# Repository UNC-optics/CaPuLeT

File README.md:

# An open-source system to integrate Calcium-imaging, Pupillometry, and Locomotion-estimated Tracking (CaPuLeT) in head-fixed mice

Designed by members of the [Pégard](https://www.nicolaspegard.com/) and [Rodríguez-Romaguera](https://www.rodriguezromagueralab.org/) Labs at the University of North Carolina at Chapel Hill, **CaPuLeT** allows researchers to capture locomotion, pupil dynamics, and body kinematics simultaneously. Our system relies on CMOS cameras, an infrared camera placed at eye-level to capture pupil size and an additional camera to record body kinematics. Our system is capable of capturing  locomotion, or the mouse's movement across time, as our wheel system is attached to a mounted rotary encoder. For more information, refer to [Ortiz-Juza et al, 2024](https://star-protocols.cell.com/protocols/3752) [1].

# Graphic User Interface (GUI)

The **CaPuLeT** MATLAB graphical user interface (GUI) allows users to trigger and manage the cameras and LEDs driven by an Arduino microcontroller with a custom shield. Within **CaPuLeT**, users can track locomotion, pupil-size, and *in vivo* calcium imaging data in real-time. 

**Behavioral and Imaging Data Collected**:
- IR Camera → Pupil Dynamics (Dilation and Constriction)
- Additional Camera → Body Kinematics (Body and Tail Movement)
- Rotary Encoder → Locomotion (Speed and Acceleration)
- Multi-Photon Microscope → Neuronal Activity (Intracellular Calcium Concentration)

# Custom Arduino Printed Circuit Board Shield:
The head-fixation wheel system is driven and controlled by an Arduino Mega 2560 microcontroller board, with a custom printed circuit board (PCB) Arduino shield with built-in resistance, interactive feedback LEDs, real-time clock compatibility, and screw hole terminals. The printed circuit board shield expands the capabilities of the microcontroller board and allows for greater stability than a conventional solderless circuit board. The Arduino shield allows users to interface with each of the components of the **CaPuLeT** GUI. 

# Commercially Available and Custom Made Parts 

The following [component list](https://github.com/UNC-optics/CaPuLeT/blob/b9dc13ef048e2fede86db514f3f39af26186ab3a/1-CaPuLeT-Components-Table.pdf) details the manufacturer, part number, and quantity of each item required. This [version](https://github.com/UNC-optics/CaPuLeT/blob/b9dc13ef048e2fede86db514f3f39af26186ab3a/2-CaPuLeT-Color-Coded-Components-Table.pdf) of the component list contains a color coded key which provides an additional layer of support when building the system. 

<table class="table table-bordered table-hover table-condensed">
<thead><tr><th title="Field #1">Part Number</th>
<th title="Field #2">Distributor</th>
<th title="Field #3">Part Name</th>
<th title="Field #4">Distributor Part Number</th>
<th title="Field #5">Quantity Needed</th>
<th title="Field #6">Unit Price</th>
<th title="Field #7">Total Price</th>
</tr></thead>
<tbody><tr>
<td align="right">1</td>
<td>McMaster</td>
<td>5 mm Linear Motion Shaft</td>
<td>6112K37</td>
<td>1</td>
<td>$10.98 </td>
<td>$10.98 </td>
</tr>
<tr>
<td align="right">2</td>
<td>McMaster</td>
<td>Clear Impact-Resistant Polycarbonate Film</td>
<td>85585K15</td>
<td>1</td>
<td>$8.35 </td>
<td>$8.35 </td>
</tr>
<tr>
<td align="right">3</td>
<td>McMaster</td>
<td>Female Threaded Round Standoff</td>
<td>93330A541</td>
<td>10</td>
<td>$2.13 </td>
<td>$21.30 </td>
</tr>
<tr>
<td align="right">4</td>
<td>McMaster</td>
<td>Socket Head Screw M3 x 0.5 mm Thread, 6 mm Long</td>
<td>91290A111</td>
<td>1 (Pack of 100)</td>
<td>$10.91 </td>
<td>$10.91 </td>
</tr>
<tr>
<td align="right">5</td>
<td>Polulu</td>
<td>Aluminum Mounting Hub for 5mm Shaft</td>
<td>1203</td>
<td>1 (Pack of 2)</td>
<td>$18.90 </td>
<td>$18.90 </td>
</tr>
<tr>
<td align="right">6</td>
<td>Polulu</td>
<td>Machine Screw: #4-40, 1/2? Length, Phillips</td>
<td>1962</td>
<td>1 (Pack of 25)</td>
<td>$1.39 </td>
<td>$1.39 </td>
</tr>
<tr>
<td align="right">7</td>
<td>Thorlabs</td>
<td>0.75 Inch Post</td>
<td>TR075</td>
<td>1</td>
<td>$5.38 </td>
<td>$5.38 </td>
</tr>
<tr>
<td align="right">8</td>
<td>Thorlabs</td>
<td>2 Inch Post</td>
<td>TR2</td>
<td>2</td>
<td>$5.90 </td>
<td>$11.80 </td>
</tr>
<tr>
<td align="right">9</td>
<td>Thorlabs</td>
<td>3 Inch Post</td>
<td>TR3</td>
<td>2</td>
<td>$6.15 </td>
<td>$12.30 </td>
</tr>
<tr>
<td align="right">10</td>
<td>Thorlabs</td>
<td>4 Inch Post, 5 Pack</td>
<td>TR4-P5</td>
<td>1 (Pack of 5)</td>
<td>$30.00 </td>
<td>$30.00 </td>
</tr>
<tr>
<td align="right">11</td>
<td>Thorlabs</td>
<td>6 Inch Post</td>
<td>TR6</td>
<td>2</td>
<td>$8.09 </td>
<td>$16.18 </td>
</tr>
<tr>
<td align="right">12</td>
<td>Thorlabs</td>
<td>8 Inch Post</td>
<td>TR8</td>
<td>2</td>
<td>$9.69 </td>
<td>$19.38 </td>
</tr>
<tr>
<td align="right">13</td>
<td>Thorlabs</td>
<td>10 Inch Post</td>
<td>TR10</td>
<td>2</td>
<td>$10.76 </td>
<td>$21.52 </td>
</tr>
<tr>
<td align="right">14</td>
<td>Thorlabs</td>
<td>2 Inch Post Holder</td>
<td>PH2</td>
<td>1</td>
<td>$8.95 </td>
<td>$8.95 </td>
</tr>
<tr>
<td align="right">15</td>
<td>Thorlabs</td>
<td>3 Inch Post Holder</td>
<td>PH3</td>
<td>4</td>
<td>$9.62 </td>
<td>$38.48 </td>
</tr>
<tr>
<td align="right">16</td>
<td>Thorlabs</td>
<td>6 Inch Post Holder</td>
<td>PH6</td>
<td>1</td>
<td>$14.70 </td>
<td>$14.70 </td>
</tr>
<tr>
<td align="right">17</td>
<td>Thorlabs</td>
<td>Right Angle End Clamp</td>
<td>RA180</td>
<td>4</td>
<td>$12.34 </td>
<td>$49.36 </td>
</tr>
<tr>
<td align="right">18</td>
<td>Thorlabs</td>
<td>Rotating Clamp</td>
<td>SWC</td>
<td>1</td>
<td>$26.91 </td>
<td>$26.91 </td>
</tr>
<tr>
<td align="right">19</td>
<td>Thorlabs</td>
<td>Right Angle Post Clamp</td>
<td>RA90TR</td>
<td>1</td>
<td>$17.82 </td>
<td>$17.82 </td>
</tr>
<tr>
<td align="right">20</td>
<td>Thorlabs</td>
<td>Mini Optical Post</td>
<td>MS3R</td>
<td>1</td>
<td>$9.09 </td>
<td>$9.09 </td>
</tr>
<tr>
<td align="right">21</td>
<td>Thorlabs</td>
<td>Aluminum Breadboard 8&quot; x 10&quot; x 1/2&quot;, 1/4&quot;-20 Taps</td>
<td>MB810</td>
<td>1</td>
<td>$131.60 </td>
<td>$131.60 </td>
</tr>
<tr>
<td align="right">22</td>
<td>Thorlabs</td>
<td>Aluminum Breadboard 12&quot; x 18&quot; x 1/2&quot;, 1/4&quot;-20 Taps</td>
<td>MB1218</td>
<td>1</td>
<td>$214.65 </td>
<td>$214.65 </td>
</tr>
<tr>
<td align="right">23</td>
<td>Thorlabs</td>
<td>Breadboard Lifting Handles, Reinforced Polymer </td>
<td>BBH1</td>
<td>2 (Pack of 2)</td>
<td>$17.01 </td>
<td>$17.01 </td>
</tr>
<tr>
<td align="right">24</td>
<td>Thorlabs</td>
<td>4-40 Stainless Steel Cap Screw, 3/8&quot; Long</td>
<td>SH4S038</td>
<td>1 (Pack of 50)</td>
<td>$9.31 </td>
<td>$9.31 </td>
</tr>
<tr>
<td align="right">25</td>
<td>Thorlabs</td>
<td>Spring-Loaded 3/16&quot; Hex-Locking Thumbscrew, 1/4&quot;-20 Thread</td>
<td>TS25H</td>
<td>2</td>
<td>$2.87 </td>
<td>$5.74 </td>
</tr>
<tr>
<td align="right">26</td>
<td>Thorlabs</td>
<td>1/4&quot;-20 Stainless Steel Setscrew, 5/8&quot; Long (Adaptor)</td>
<td>SS25S0625</td>
<td>1 (Pack of 25)</td>
<td>$6.97 </td>
<td>$6.97 </td>
</tr>
<tr>
<td align="right">27</td>
<td>Thorlabs</td>
<td>1/4&quot; Washer, M6 Compatible, Stainless Steel</td>
<td>W25S050</td>
<td>1 (Pack of 100)</td>
<td>$10.20 </td>
<td>$10.20 </td>
</tr>
<tr>
<td align="right">28</td>
<td>Thorlabs</td>
<td>1/4&quot;-20 Stainless Steel Nut</td>
<td>N25S0440</td>
<td>1 (Pack of 50)</td>
<td>$6.43 </td>
<td>$6.43 </td>
</tr>
<tr>
<td align="right">29</td>
<td>Omron</td>
<td>Rotary Encoder - 1024 P/R (Quadrature)</td>
<td>E6B2-CWZ3E (E69-C06B)</td>
<td>1</td>
<td>$48.50 </td>
<td>$48.50 </td>
</tr>
<tr>
<td align="right">30</td>
<td>DB Unlimited</td>
<td>Speaker 80hm 5 w top port 104db</td>
<td>2104-SP500208-3-ND</td>
<td>1</td>
<td>$6.79 </td>
<td>$6.79 </td>
</tr>
<tr>
<td align="right">31</td>
<td>SullinsCorp</td>
<td>2.54mm Pitch Single Row Pin Header Strip</td>
<td>PREC040SAAN-RC</td>
<td>3</td>
<td>$1.53</td>
<td>$1.53</td>
</tr>
<tr>
<td align="right">32</td>
<td>Ardest</td>
<td>2N2222 NPN TO-92 Power Transistors</td>
<td>2N2222</td>
<td>6</td>
<td>$1.44</td>
<td>$1.44</td>
</tr>
<tr>
<td align="right">33</td>
<td>Boca Bearings</td>
<td>5 mm Steel Ball Bearing</td>
<td>SMR115-ZZC #5 LD</td>
<td>2</td>
<td>$10.58 </td>
<td>$21.16 </td>
</tr>
<tr>
<td align="right">34</td>
<td>Xenocam</td>
<td>9-22mm 1/3" F1.4 M12-mount lens with IR filter</td>
<td>XC0922LENS</td>
<td>1</td>
<td>$19.99 </td>
<td>$19.99 </td>
</tr>
<tr>
<td align="right">35</td>
<td>Monoprice</td>
<td>USB 2.0 Type-A Male to Mini-B 5pin Male Cable (Monoprice)</td>
<td>B002KL8J8W</td>
<td>1</td>
<td>$4.78</td>
<td>$4.78</td>
</tr>
<tr>
<td align="right">36</td>
<td>Computar</td>
<td>0.33-Inch Varifocal lens 2.8-12mm F1.3 Auto Iris (Computar)</td>
<td>B002HRE2ZS / TG4Z2813FCS-IR</td>
<td>1(Used)</td>
<td>$19.99 </td>
<td>$19.99 </td>
</tr>
<tr>
<td align="right">37</td>
<td>Chanzon</td>
<td>3 mm UV light, 395-400nm (Chanzon)</td>
<td>100F3T-YT-WH-PU</td>
<td>1 (Pack of 100)</td>
<td>$6.99 </td>
<td>$6.99 </td>
</tr>
<tr>
<td align="right">38</td>
<td>Adafruit</td>
<td>5 mm super-bright IR LED, 940nm (Adafruit)</td>
<td>ADA388 / B00ULB0U44</td>
<td>1 (Pack of 25)</td>
<td>$10.98 </td>
<td>$10.98 </td>
</tr>
<tr>
<td align="right">39</td>
<td>Fermerry</td>
<td>24 AWG 50 feet Electrical Wire (Fermerry)</td>
<td>B089CX3FVV</td>
<td>1</td>
<td>$26.99 </td>
<td>$26.99 </td>
</tr>
<tr>
<td align="right">40</td>
<td>Arduino</td>
<td>Arduino Mega 2560 Rev3 Microcontroller Board (Arduino)</td>
<td>A000067 / B0046AMGW0</td>
<td>1</td>
<td>$48.99 </td>
<td>$48.99 </td>
</tr>
<tr>
<td align="right">41</td>
<td>Arduino</td>
<td>USB 2.0 Cable Type A/B (Arduino)</td>
<td>M000006 / B013EOQUAW</td>
<td>1</td>
<td>$7.00 </td>
<td>$7.00 </td>
</tr>
<tr>
<td align="right">42</td>
<td>Tnisesm</td>
<td>PCB Mount Screw Terminal Block Connectors (Tnisesm)</td>
<td>CATN-T03B</td>
<td>1</td>
<td>$8.99 </td>
<td>$8.99 </td>
</tr>
<tr>
<td align="right">43</td>
<td>Adeep</td>
<td>Real Time Clock Module DS3231 AT24C32 IIC (Adeept)</td>
<td>2pcsDS3231 / B097PMNMQZ</td>
<td>1 (Pack of 2)</td>
<td>$7.99 </td>
<td>$7.99 </td>
</tr>
<tr>
<td align="right">44</td>
<td>LiCB</td>
<td>3V Lithium Battery (Junpower)</td>
<td>CR2032 / B07LGL9LQ1</td>
<td>1 (Pack of 10)</td>
<td>$4.99 </td>
<td>$4.99 </td>
</tr>
<tr>
<td align="right">45</td>
<td>ELECFUN</td>
<td>Heat Shrink Tubing (Electfun)</td>
<td>RSG-KIT350</td>
<td>1</td>
<td>$14.99 </td>
<td>$14.99 </td>
</tr>
<tr>
<td align="right">46</td>
<td>Yancorp</td>
<td>Black Adhesive contact paper (Yancorp)</td>
<td>B082CPSVPW</td>
<td>1</td>
<td>$6.98 </td>
<td>$6.98 </td>
</tr>
<tr>
<td align="right">47</td>
<td>Weld-On</td>
<td>IPS Weld-On 3 Acrylic Plastic Cement (Weld-On)</td>
<td>?TLLPN-21847771</td>
<td>1</td>
<td>$28.55 </td>
<td>$28.55 </td>
</tr>
<tr>
<td align="right">48</td>
<td>CENTROPOWER</td>
<td>12V 5A DC Power Cable Male Female Connector (Centro Power)</td>
<td>DCCORD-MF</td>
<td>1 (Pack of 10)</td>
<td>$9.19 </td>
<td>$9.19 </td>
</tr>
<tr>
<td align="right">49</td>
<td>CENTROPOWER</td>
<td>12V DC Power Connector Barrel Adaptor (Centro Power)</td>
<td>B07C61434H</td>
<td>1 (Pack of 10)</td>
<td>$7.99 </td>
<td>$7.99 </td>
</tr>
<tr>
<td align="right">50</td>
<td>ALITOVE</td>
<td>12V Red LED Flexible Strip Ribbon Light (Alitrove, 16.4 feet)</td>
<td>AL5RWPBK12V</td>
<td>1</td>
<td>$13.99 </td>
<td>$13.99 </td>
</tr>
<tr>
<td align="right">51</td>
<td>Mifasopower</td>
<td>Power Strip Surge Protector 10Ft (Mifaso Power)</td>
<td>MFS311T</td>
<td>1</td>
<td>$19.99 </td>
<td>$19.99 </td>
</tr>
<tr>
<td align="right">52</td>
<td>Sumato Stuff</td>
<td>Anti Vibration Pads (Functional Necessities)</td>
<td>SSHI00003</td>
<td>1 (Pack of 4)</td>
<td>$14.99 </td>
<td>$14.99 </td>
</tr>
<tr>
<td align="right">53</td>
<td>Focusound</td>
<td>1&quot; x 12&quot; x 12&quot; Sound Absorption Wall Panels (Xin &amp; Log)</td>
<td>FS0302A</td>
<td>1 (Pack of 24)</td>
<td>$17.99 </td>
<td>$17.99 </td>
</tr>
<tr>
<td align="right">54</td>
<td>TANTTI</td>
<td>4 inch Zip Ties with 18 lb Tensile Strength</td>
<td>604477847283</td>
<td>1 (Pack of 200)</td>
<td>$3.99 </td>
<td>$3.99 </td>
</tr>
<tr>
<td align="right">55</td>
<td>3M</td>
<td>3M Scotch Super 33+ Electrical Tape - 3/4 in x 52 ft</td>
<td>MMM06133</td>
<td>1</td>
<td>$4.98 </td>
<td>$4.98 </td>
</tr>
<tr>
<td align="right">56</td>
<td>Amazon</td>
<td>Hirose 4 Pin Female HR10A-7P-4S to Flying Leads Power Cable (Alvin’s Cables)</td>
<td>HR10A-7P-4S(73)</td>
<td>1</td>
<td>$25.99 </td>
<td>$25.99</td>
</tr>
<tr>
<td align="right">57</td>
<td>Custom Machined Parts</td>
<td>Rotary Encoder Adaptor (Aluminum 304)</td>
<td>CNC Machining (eMachineShop)</td>
<td>6 (Bulk Purchase)</td>
<td>$28.43 </td>
<td>$170.62 </td>
</tr>
<tr>
<td align="right">58</td>
<td>Custom Machined Parts</td>
<td>Head Plate Holder (Aluminum 304)</td>
<td>CNC Machining (eMachineShop)</td>
<td>12 (Bulk Purchase)</td>
<td>$30.20 </td>
<td>$362.44 </td>
</tr>
<tr>
<td align="right">59</td>
<td>Custom Machined Parts</td>
<td>Head Plate (Top Piece) (Aluminum 304)</td>
<td>CNC Machining (eMachineShop)</td>
<td>6 (Bulk Purchase)</td>
<td>$39.14 </td>
<td>$234.85 </td>
</tr>
<tr>
<td align="right">60</td>
<td>Custom Machined Parts</td>
<td>Head Plate (Bottom Piece) (Aluminum 304)</td>
<td>CNC Machining (eMachineShop)</td>
<td>6 (Bulk Purchase)</td>
<td>$51.01 </td>
<td>$306.04 </td>
</tr>
<tr>
<td align="right">61</td>
<td>Custom Machined Parts</td>
<td>Head rings (Aluminum 6061-T6)</td>
<td>CNC Machining (eMachineShop)</td>
<td>100 (Bulk Purchase)</td>
<td>$5.16 </td>
<td>$258.22 </td>
</tr>
<tr>
<td align="right">62</td>
<td>Custom Machined Parts</td>
<td>Rotary Wheel (1/8 Thick Clear Cast Acrylic)</td>
<td>Laser Cutting (Ponoko)</td>
<td>2</td>
<td>$61.06 </td>
<td>$61.06 </td>
</tr>
<tr>
<td align="right">63</td>
<td>Custom Machined Parts</td>
<td>Rotary Wheel Curved Surface (Clear Cast Acrylic)</td>
<td>Laser Cutting / Manual Cutting</td>
<td>1</td>
<td>$0.00 </td>
<td>$0.00 </td>
</tr>
<tr>
<td align="right">64</td>
<td>Custom Machined Parts</td>
<td>Rotary Wheel Curved Surface (Black Adhesive Contact Paper)</td>
<td>Laser Cutting / Manual Cutting</td>
<td>1</td>
<td>$0.00 </td>
<td>$0.00 </td>
</tr>
<tr>
<td align="right">65</td>
<td>Custom Machined Parts</td>
<td>Waste Management Ramp (Resin)</td>
<td>3-D Printing (Craftcloud3d)</td>
<td>1</td>
<td>$57.76 </td>
<td>$57.76 </td>
</tr>
<tr>
<td align="right">66</td>
<td>Custom Machined Parts</td>
<td>Arduino Mega 2560 Rev3 Protective Case (Resin)</td>
<td>3-D Printing (Craftcloud3d)</td>
<td>1</td>
<td>$16.06 </td>
<td>$16.06 </td>
</tr>
<tr>
<td align="right">67</td>
<td>Custom Machined Parts</td>
<td>Arduino Mega 2560 Rev3 Shield SMT PCB</td>
<td>PCB Manufacturing (JLC PCB)</td>
<td>1</td>
<td>X</td>
<td>X</td>
</tr>
<tr>
<td align="right">68</td>
<td>FLIR</td>
<td>Firefly S Camera</td>
<td>FFY-U3-16S2M-S</td>
<td>1</td>
<td>$234.00 </td>
<td>$234.00 </td>
</tr>
<tr>
<td align="right">69</td>
<td>FLIR</td>
<td>Tripod Adapter for Firefly S Camera</td>
<td>ACC-01-0017</td>
<td>1</td>
<td>$32.10 </td>
<td>$32.10 </td>
</tr>
<tr>
<td align="right">70</td>
<td>FLIR</td>
<td>USB 3.1 Locking Cable</td>
<td>ACC-01-2300</td>
<td>1</td>
<td>$24.60 </td>
<td>$24.60 </td>
</tr>
<tr>
<td align="right">71</td>
<td>FLIR</td>
<td>GPIO cable w/ 6 pins</td>
<td>ACC-01-3015</td>
<td>1</td>
<td>$9.60 </td>
<td>$9.60 </td>
</tr>
<tr>
<td align="right">72</td>
<td>The Imaging Source</td>
<td>USB 2.0 CMOS Monochrome Camera</td>
<td>DMK-22BUC03</td>
<td>1</td>
<td>$234.00 </td>
<td>$234.00 </td>
</tr>
<tr>
<td align="right">73</td>
<td>SYSRACKS</td>
<td>15U 35&quot; Depth Under Desk Sound Proof Server Cabinet</td>
<td>SP15.900</td>
<td>1</td>
<td>$1,122.00 </td>
<td>$1,122.00 </td>
</tr>
</tbody></table>

This [document](https://github.com/UNC-optics/CaPuLeT/blob/b9dc13ef048e2fede86db514f3f39af26186ab3a/4-CaPuLeT-Custom-Parts-Table.pdf) outlines the design of each of the custom pieces and the file types found within this repository that can be used to replicate the system. More details regarding the specifications of the custom parts can be found [here](https://github.com/UNC-optics/CaPuLeT/blob/b9dc13ef048e2fede86db514f3f39af26186ab3a/5-CaPuLeT-Custom-Parts-Specifications.pdf). The following [spreadsheet](https://github.com/UNC-optics/CaPuLeT/blob/b9dc13ef048e2fede86db514f3f39af26186ab3a/3-CaPuLeT-Cost-Spreadsheet.xlsx) outlines the total cost of the system.  

**Here is a list of the manufacturers we purchased materials from:** 
- McMaster-Carr
- Pololu
- Thorlabs
- SparkFun
- Digikey
- Amazon
- FLIR
- The Imaging Source
- SYSRACKS

**Here is a list of companies you can purchase custom parts from, if not fabricated in-house:**
- eMachineShop (CNC Machining)
- Ponoko (Laser Cutting)
- Craftcloud3d (3-D Printing)
- JBL PCB (PCB Printing / Soldering)

# Step-by-Step Building Guide

**A fully functioning system requires users to build the following elements from the materials purchased:**
- Locomotion Wheel
- Headplate Fixation System
- IR / UV LEDs

**Additionally, the following commercial materials need to modified to be used within our system:**
- Rotary Encoder
- GPIO Cable
- Hirose Cable
- Overhead Speaker
- Ambient Noise Fan
- Red LED Strips

This following [guide](https://github.com/UNC-optics/CaPuLeT/blob/b9dc13ef048e2fede86db514f3f39af26186ab3a/6-CaPuLeT-Step-by-Step-Guide.pdf) provides a step-by-step walkthrough for building and modifying each of the required components. This document includes diagrams and explanations for assembling each of the final components of the build. 

# Software Installation Guide and Dependencies

Following this installation guide will ensure that your system will be able to run the set of MATLAB scripts and Arduino IDE sketches we have provided. Our system is run primarily on MATLAB's interface. While other software is used to first initialize components, such as Arduino IDE for the rotary encoder and Spinnaker SDK for the cameras, the subsequent input signals and data acquisition steps are performed exclusively with MATLAB. 

**Required Software and Applications**:
- [MATLAB R2022a](https://www.mathworks.com/products/new_products/release2022a.html)
- [Arduino IDE](https://www.arduino.cc/en/software)
- [Spinnaker SDK](https://www.flir.com/products/spinnaker-sdk/)
- [DeepLabCuts](https://github.com/DeepLabCut/DeepLabCut)
  
Our MATLAB scripts are based on MATLAB R2022a, a previous version of the software application. Running our scripts on a more recent version of the application will result in a number of errors. After downloading MATLAB R2022a, you will need to download a number of toolboxes and add-ons. 

**Base Toolboxes**:
- Data Acquisition Toolbox
- Image Acquisition Toolbox
- Image Processing Toolbox
- Statistics and Machine Learning Toolbox 

**Additional Toolbox Support Packages**:
- Data Acquisition Toolbox Support Package for National Instruments NI-DAQmx Devices
- Image Acquisition Toolbox Support Package for GenICam Interface
- Image Acquisition Toolbox Support Package OS Generic Video Interface
- Image Acquisition Toolbox Support Package for Point Grey Hardware
- Image Acquisition Toolbox Support Support Package for GigE Vision Hardware
- MATLAB Support Package for Arduino Hardware

Finally, users will need to download the following drivers to generate a connection between their computer system and an external hardware device. In our case, we need to download two drivers to interface with the additional camera used in our system.

**Driver Requirements**:
- USB3 Driver
- [DMK 22BUC03 Driver](https://www.oemcameras.com/dmk-22buc03.htm)
- [Spinnaker SDK USB3 Vision Cameras Driver](https://www.flir.com/products/spinnaker-sdk/)
- [IC Matlab Plugin for Matlab (Version 3.4.0.58)](https://www.theimagingsource.com/en-us/support/download/icmatlabr2013b-3.4.0.58/)

**Library Requirements**:
- [DS3231 Library](https://github.com/NorthernWidget/DS3231)
  
# Contact

Further information and requests for resources should be directed to and will be fulfilled by the lead contact and corresponding author, Jose Rodriguez-Romaguera (jose_rodriguezromaguera@med.unc.edu). Example pupillometric and locomotion data is available upon request to the technical contact and corresponding author, Nicolas C. Pégard (pegard@unc.edu).

# Citation 

If you replicate this system in your own labs or use parts of our designs and code, we kindly ask that you please cite [Ortiz-Juza et al, 2024](https://star-protocols.cell.com/protocols/3752) [1]. 

[1] Ortiz-Juza, M. M., Tormes-Vaquerano, J., Hegel, S. M., Curtis, V. R., Alghorazi, R. A., Miller, N. W., McTaggart, E. M., Pégard, N. C., & Rodriguez-Romaguera, J. (2024). Protocol for an open-source system to integrate calcium imaging, pupillometry, and locomotion-estimated tracking in head-fixed mice. STAR Protocols, 5(4), 103331. https://doi.org/10.1016/j.xpro.2024.103331

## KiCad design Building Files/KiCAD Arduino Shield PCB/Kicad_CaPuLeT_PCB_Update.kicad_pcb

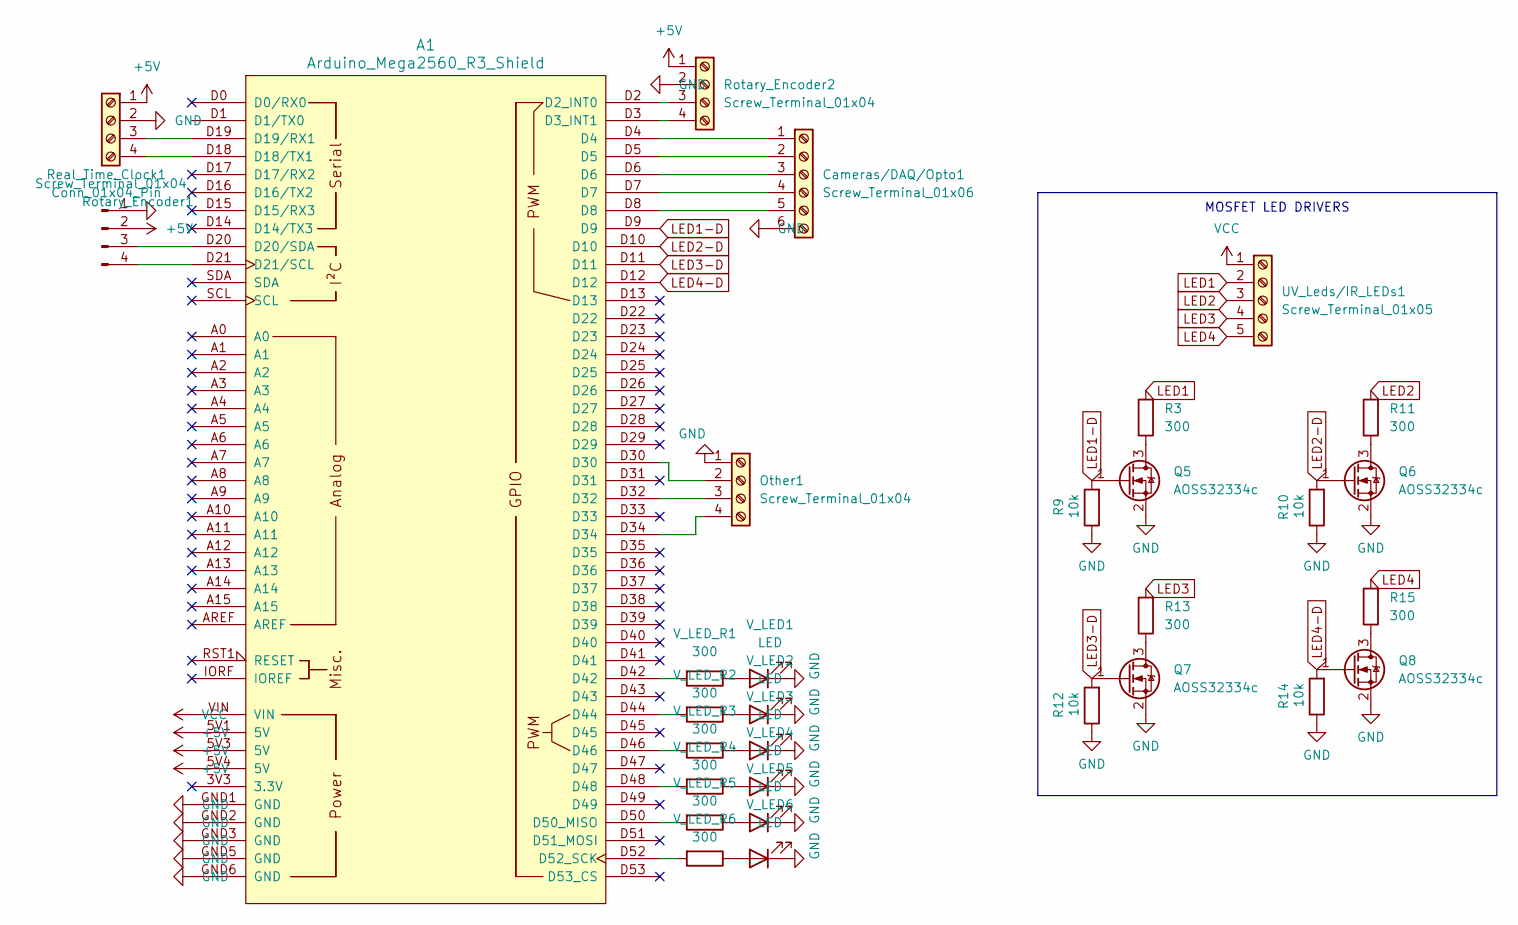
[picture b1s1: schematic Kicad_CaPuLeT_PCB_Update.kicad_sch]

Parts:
A1: Arduino_Mega2560_R3_Shield; Arduino_Mega2560_R3_Shield_Reduced_Hole
Cameras/DAQ/Opto1: Screw_Terminal_01x06; TerminalBlock_Phoenix_MKDS-1,5-6_1x06_P5.00mm_Horizontal
Other1: Screw_Terminal_01x04; TerminalBlock_Phoenix_MKDS-1,5-4_1x04_P5.00mm_Horizontal
Q5, Q6, Q7, Q8: AOSS32334c; SOT-23
R3, R11, R13, R15: 300; R_0805_2012Metric
R9, R10, R12, R14: 10k; R_0805_2012Metric
Real_Time_Clock1: Conn_01x04_Pin; PinHeader_1x04_P2.54mm_Vertical
Rotary_Encoder1, Rotary_Encoder2: Screw_Terminal_01x04; TerminalBlock_Phoenix_MKDS-1,5-4_1x04_P5.00mm_Horizontal
UV_Leds/IR_LEDs1: Screw_Terminal_01x05; TerminalBlock_Phoenix_MKDS-1,5-5_1x05_P5.00mm_Horizontal
V_LED1, V_LED2, V_LED3, V_LED4, V_LED5, V_LED6: LED; LED_0805_2012Metric
V_LED_R1, V_LED_R2, V_LED_R3, V_LED_R4, V_LED_R5, V_LED_R6: 300; R_0805_2012Metric

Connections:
+5V: A1.5V1 (5V), A1.5V3 (5V), A1.5V4 (5V), Real_Time_Clock1.2, Rotary_Encoder1.1, Rotary_Encoder2.1
GND: A1.GND1 (GND), A1.GND2 (GND), A1.GND3 (GND), A1.GND5 (GND), A1.GND6 (GND), Cameras/DAQ/Opto1.6, Other1.1, Q5.2 (S), Q6.2 (S), Q7.2 (S), Q8.2 (S), R9.1, R10.1, R12.1, R14.1, Real_Time_Clock1.1, Rotary_Encoder1.2, Rotary_Encoder2.2, V_LED1.1 (K), V_LED2.1 (K), V_LED3.1 (K), V_LED4.1 (K), V_LED5.1 (K), V_LED6.1 (K)
LED1: R3.2, UV_Leds/IR_LEDs1.2
LED1-D: A1.D9, Q5.1 (G), R9.2
LED2: R11.2, UV_Leds/IR_LEDs1.3
LED2-D: A1.D10, Q6.1 (G), R10.2
LED3: R13.2, UV_Leds/IR_LEDs1.4
LED3-D: A1.D11, Q7.1 (G), R12.2
LED4: R15.2, UV_Leds/IR_LEDs1.5
LED4-D: A1.D12, Q8.1 (G), R14.2
unnamed: A1.D2 (D2_INT0), Rotary_Encoder2.3
unnamed: A1.D3 (D3_INT1), Rotary_Encoder2.4
unnamed: A1.D18 (D18/TX1), Rotary_Encoder1.4
unnamed: A1.D19 (D19/RX1), Rotary_Encoder1.3
unnamed: A1.D20 (D20/SDA), Real_Time_Clock1.3
unnamed: A1.D21 (D21/SCL), Real_Time_Clock1.4
unnamed: A1.D50 (D50_MISO), V_LED_R5.2
unnamed: A1.D52 (D52_SCK), V_LED_R6.2
unnamed: A1.D42, V_LED_R1.2
unnamed: A1.D44, V_LED_R2.2
unnamed: A1.D46, V_LED_R3.2
unnamed: A1.D48, V_LED_R4.2
unnamed: A1.D4, Cameras/DAQ/Opto1.1
unnamed: A1.D5, Cameras/DAQ/Opto1.2
unnamed: A1.D6, Cameras/DAQ/Opto1.3
unnamed: A1.D7, Cameras/DAQ/Opto1.4
unnamed: A1.D8, Cameras/DAQ/Opto1.5
unnamed: A1.D30, Other1.2
unnamed: A1.D32, Other1.3
unnamed: A1.D34, Other1.4
unnamed: Q5.3 (D), R3.1
unnamed: Q6.3 (D), R11.1
unnamed: Q7.3 (D), R13.1
unnamed: Q8.3 (D), R15.1
unnamed: V_LED1.2 (A), V_LED_R1.1
unnamed: V_LED2.2 (A), V_LED_R2.1
unnamed: V_LED3.2 (A), V_LED_R3.1
unnamed: V_LED4.2 (A), V_LED_R4.1
unnamed: V_LED5.2 (A), V_LED_R5.1
unnamed: V_LED6.2 (A), V_LED_R6.1
VCC: A1.VIN, UV_Leds/IR_LEDs1.1

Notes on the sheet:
MOSFET LED DRIVERS

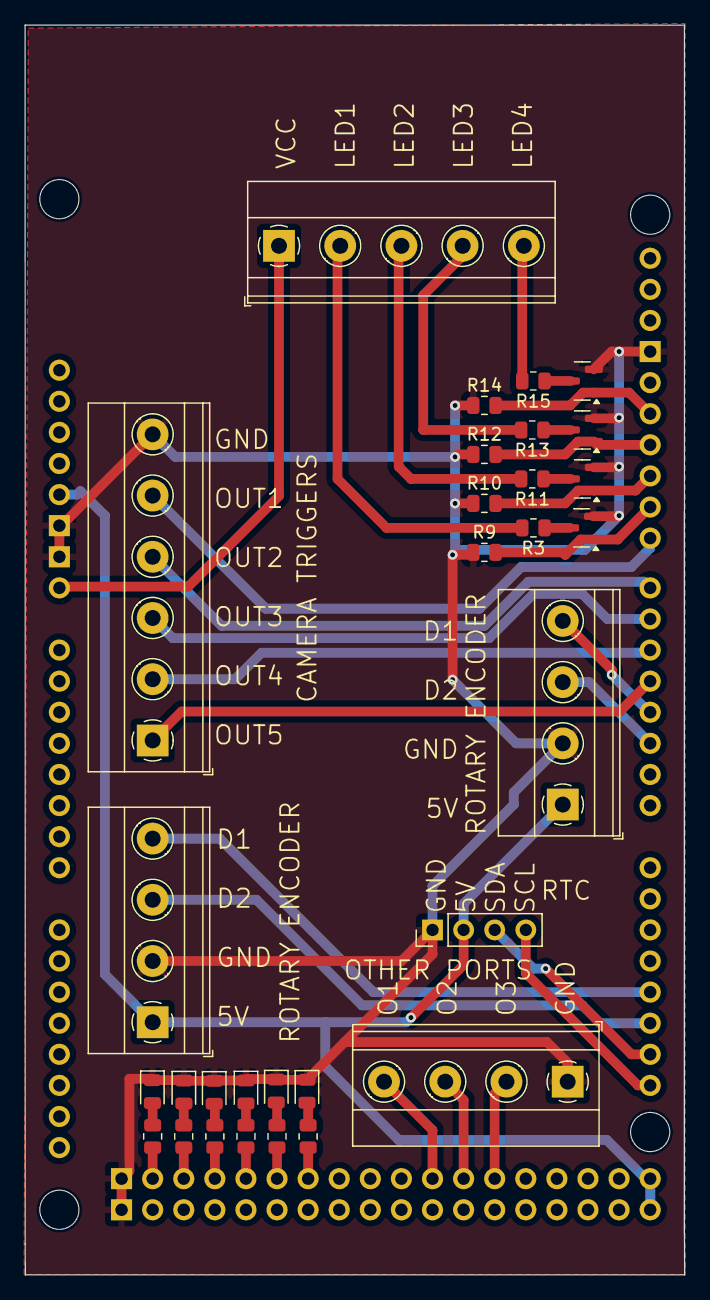
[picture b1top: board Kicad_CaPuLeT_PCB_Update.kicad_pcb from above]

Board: 2 copper layers, 53.9 x 102.1 mm, 31 parts (0 on the bottom side), 41 nets.

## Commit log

2024-01-08 Rename a) Pupillometry Components Table.pdf to Pupillometry Components Table.pdf
2024-01-08 Rename Pupillometry Components Table.pdf to 1. Pupillometry Components Table.pdf
2024-01-08 Rename 1. Pupillometry Components Table.pdf to 1-Pupillometry Components Table.pdf
2024-01-08 Rename 1-Pupillometry Components Table.pdf to 1-Pupillometry-Components-Table.pdf
2024-01-08 Rename 1-Pupillometry-Components-Table.pdf to a-Pupillometry-Components-Table.pdf
2024-01-08 Rename a-Pupillometry-Components-Table.pdf to 1-Pupillometry-Components-Table.pdf
2024-01-08 Rename b) Color Coded Pupillometry Components Table.pdf to 2-Color-Coded-Pupillometry Components-Table.pdf
2024-01-08 Rename c) Pupillometry Wheel Cost Spreadsheet.xlsx to 3-Pupillometry-Wheel-Cost-Spreadsheet.xlsx
2024-01-08 Rename d) Pupillometry Wheel Custom Parts Specifications.pdf to 4-Pupillometry-Wheel-Custom-Parts-Specifications.pdf
2024-01-08 Rename e) Pupillometry Wheel Machined Parts Table.pdf to 5-Pupillometry-Wheel-Machined-Parts-Table.pdf
2024-01-08 Rename 2-Color-Coded-Pupillometry Components-Table.pdf to 2-Color-Coded-Pupillometry-Components-Table.pdf
2024-01-08 Rename 5-Pupillometry-Wheel-Machined-Parts-Table.pdf to 4-Pupillometry-Wheel-Machined-Parts-Table.pdf
2024-01-08 Rename 4-Pupillometry-Wheel-Custom-Parts-Specifications.pdf to 5-Pupillometry-Wheel-Custom-Parts-Specifications.pdf
2024-01-08 Rename 4-Pupillometry-Wheel-Machined-Parts-Table.pdf to 4-Pupillometry-Wheel-Custom-Parts-Table.pdf
2024-01-08 Rename d) Pupillometry Wheel Custom Parts Specifications.pdf to 5-Pupillometry-Wheel-Custom-Parts-Specifications.pdf
2024-01-08 Rename e) Pupillometry Wheel Machined Parts Table.pdf to 4-Pupillometry-Wheel-Custom-Parts-Table.pdf
2024-01-09 Create A
2024-02-24 a.html
2024-07-16 Create KiCAD Arduino Shield PCB
2024-07-16 Add File for CaPuLeT GUI
2024-07-16 Add R_scripts used to analyze some data in CaPuLeT Protocol Paper
2024-07-16 Add Spinview settings for CaPuLeT Protocol Paper
2024-07-16 Removing old folder of code scripts
2024-08-18 Update CalciumImaging_Script.R
    Fixed the overlap in numbers for the x-axis in the neural heatmap figures
2024-08-19 Add files via upload
    Update to Neural Heatmap figure so that x-axis labels do not overlap.

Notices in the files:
README.md:
Citation:
If you replicate this system in your own labs or use parts of our designs and code, we kindly ask that you please cite [Ortiz-Juza et al, 2024](https://star-protocols.cell.com/protocols/3752) [1].
[1] Ortiz-Juza, M. M., Tormes-Vaquerano, J., Hegel, S. M., Curtis, V. R., Alghorazi, R. A., Miller, N. W., McTaggart, E. M., Pégard, N. C., & Rodriguez-Romaguera, J. (2024). Protocol for an open-source system to integrate calcium imaging, pupillometry, and locomotion-estimated tracking in head-fixed mice. STAR Protocols, 5(4), 103331. https://doi.org/10.1016/j.xpro.2024.103331
